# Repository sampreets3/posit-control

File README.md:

# posit-control

Posit is an STM32-based DC motor controller designed to provide an efficient and reliable solution for controlling DC motors in various applications. This README file provides an overview of the Posit motor controller, its features, and instructions on getting started and using it in your projects.

---

## Features

- __STM32F1 Microcontroller:__ Posit is built around the STM32F103 microcontroller, known for its reliability and high-performance capabilities.

__USB Control:__ Posit acts as a USB Virtual COM Port, for sending over commands via usb->serial interfaces.

__UART Communication:__ UART interface for communication with external devices or microcontrollers.

---

## Usage

The Posit STM32 DC Motor Controller is highly customizable to fit a wide range of applications. You can control the motor speed and direction using PWM signals, monitor current feedback, and interface with external sensors for more advanced control.

Here is a basic example of controlling a motor using Posit:

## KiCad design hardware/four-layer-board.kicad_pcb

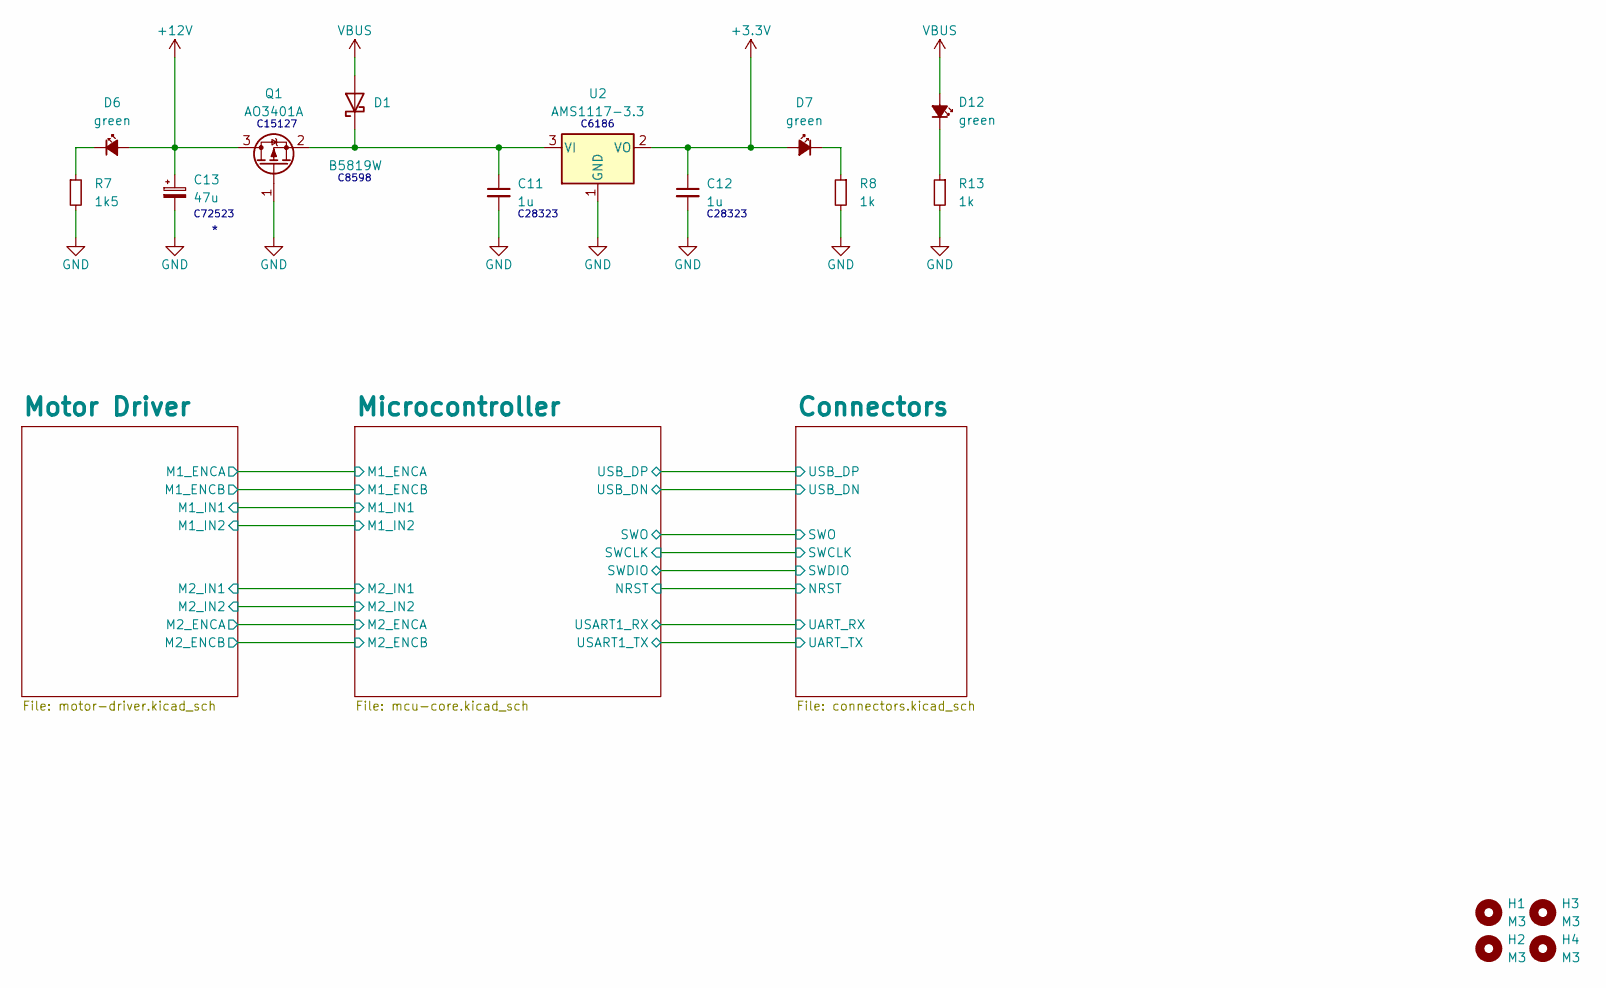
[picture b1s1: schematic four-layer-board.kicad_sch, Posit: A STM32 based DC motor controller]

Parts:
C11, C12: 1u; C_0805_2012Metric
C13: 47u; CP_Elec_6.3x7.7
D1: B5819W; D_SOD-123
D6, D7, D12: green; LED_0603_1608Metric
H1, H2, H3, H4: M3; MountingHole_3.2mm_M3_DIN965_Pad
Q1: AO3401A; SOT-23
R7: 1k5; R_0603_1608Metric
R8, R13: 1k; R_0603_1608Metric
U2: AMS1117-3.3; SOT-223-3_TabPin2

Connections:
+3.3V: C12.1, D7.2 (A), U2.2 (VO); also elsewhere on the board
+12V: C13.1, D6.2 (A), Q1.3 (D); also elsewhere on the board
GND: C11.2, C12.2, C13.2, Q1.1 (G), R7.2, R8.2, R13.2, U2.1 (GND); also elsewhere on the board
unnamed: C11.1, D1.1 (K), Q1.2 (S), U2.3 (VI)
unnamed: D6.1 (K), R7.1
unnamed: D7.1 (K), R8.1
unnamed: D12.1 (K), R13.1
VBUS: D1.2 (A), D12.2 (A); also elsewhere on the board

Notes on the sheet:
C28323
C6186
C15127
C8598
C72523

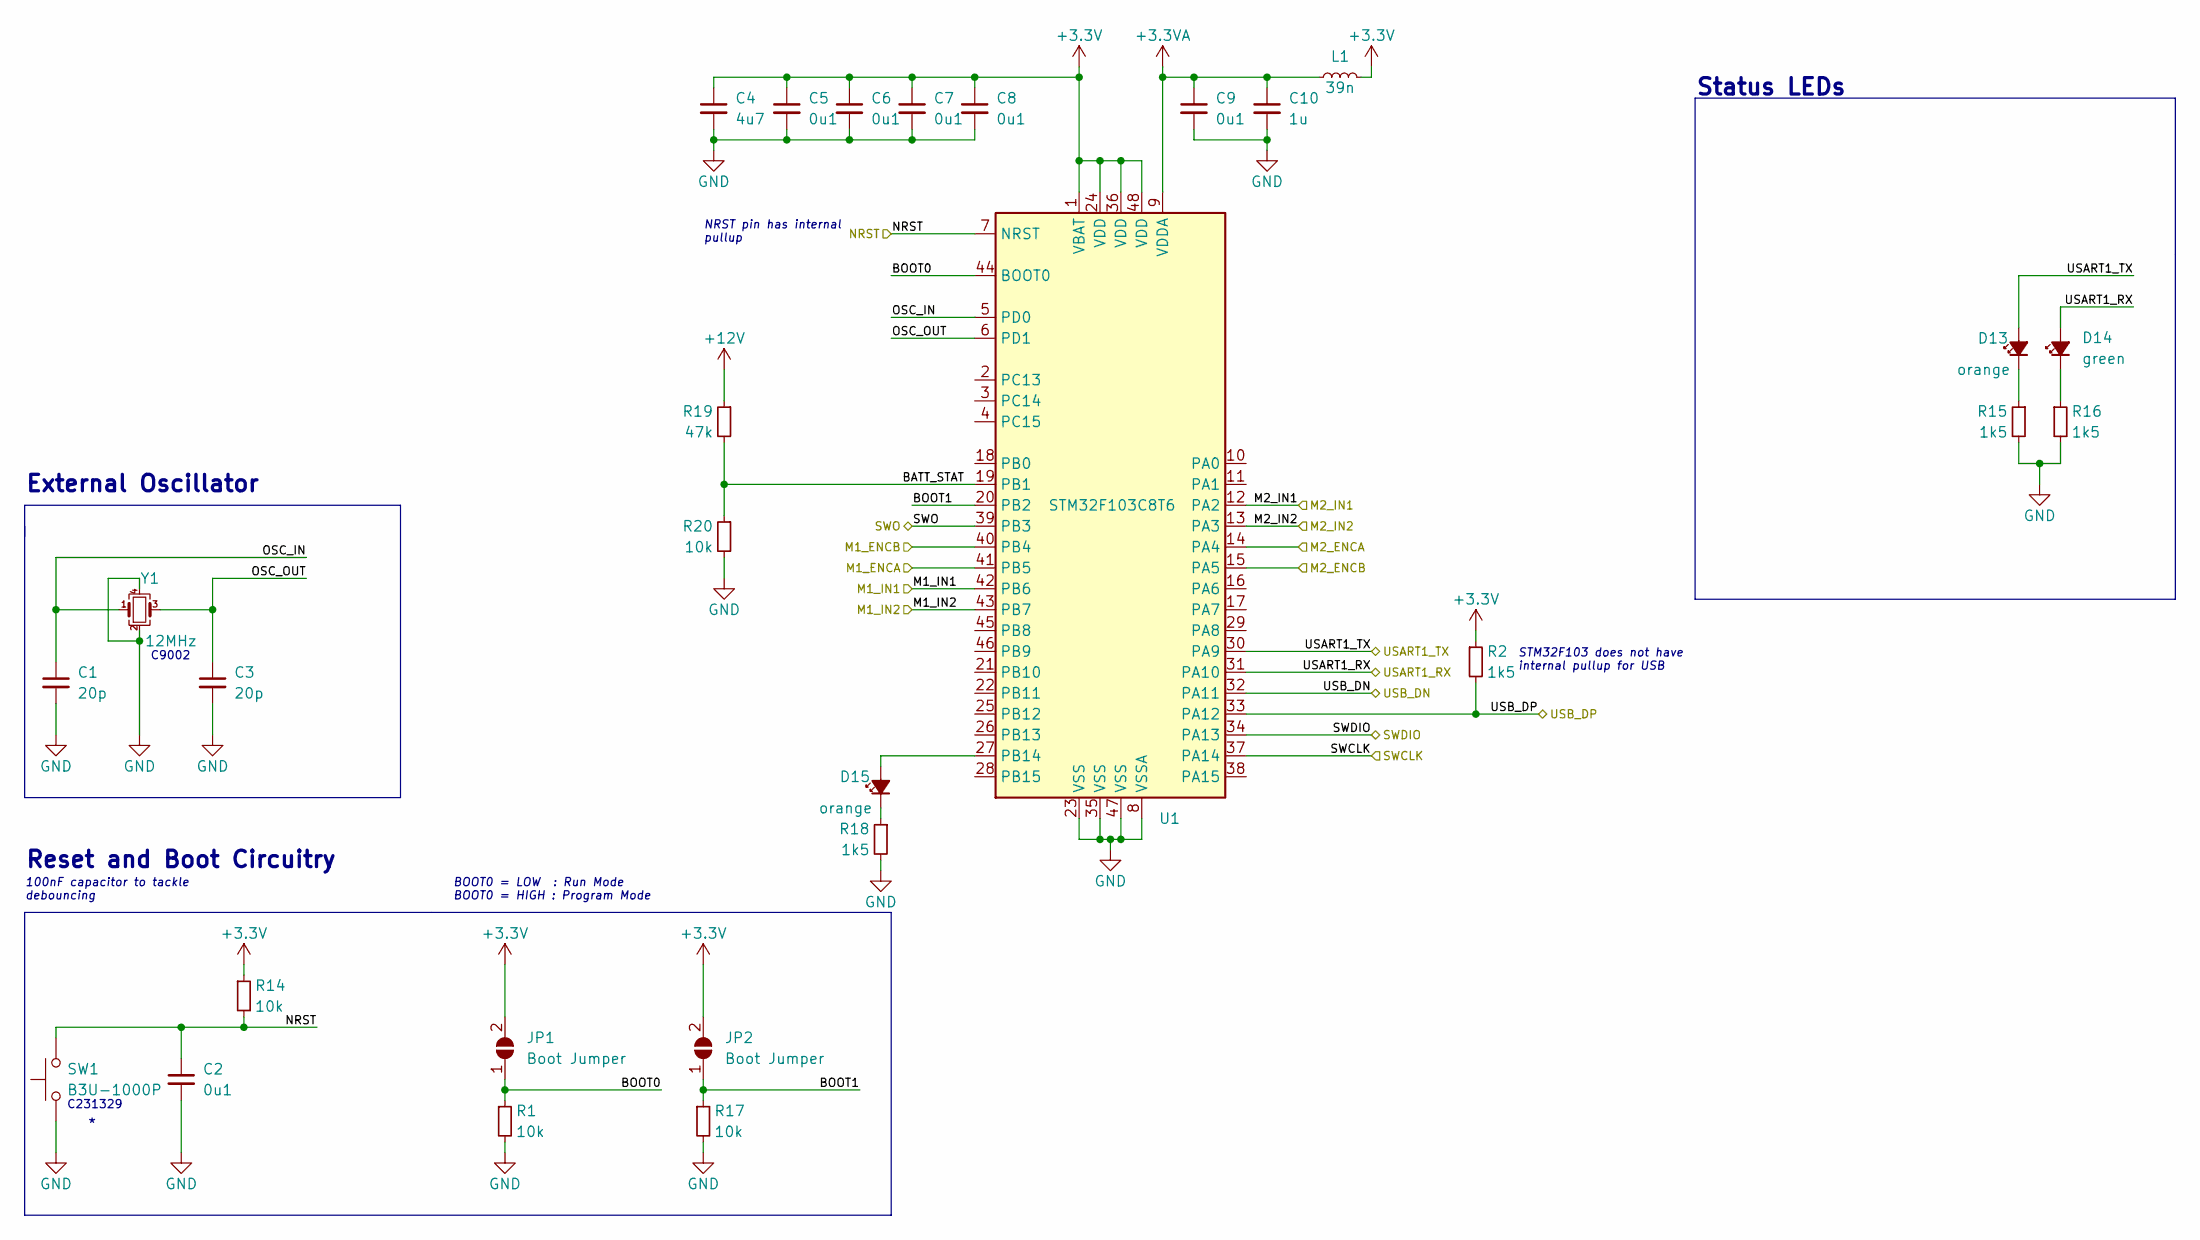
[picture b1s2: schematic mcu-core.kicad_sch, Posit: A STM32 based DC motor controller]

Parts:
C1, C3: 20p; C_0402_1005Metric
C2, C5, C6, C7, C8, C9: 0u1; C_0402_1005Metric
C4: 4u7; C_0603_1608Metric
C10: 1u; C_0402_1005Metric
D13, D15: orange; LED_0603_1608Metric
D14: green; LED_0603_1608Metric
JP1, JP2: Boot Jumper; SolderJumper-2_P1.3mm_Open_Pad1.0x1.5mm
L1: 39n; L_0603_1608Metric
R1, R14, R17: 10k; R_0402_1005Metric
R2, R15, R16, R18: 1k5; R_0402_1005Metric
R19: 47k; R_0603_1608Metric_Pad0.98x0.95mm_HandSolder
R20: 10k; R_0603_1608Metric_Pad0.98x0.95mm_HandSolder
SW1: B3U-1000P; SW_SPST_B3U-1000P
U1: STM32F103C8T6; LQFP-48_7x7mm_P0.5mm
Y1: 12MHz; Crystal_SMD_3225-4Pin_3.2x2.5mm

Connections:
+3.3V: C4.1, C5.1, C6.1, C7.1, C8.1, JP1.2 (B), JP2.2 (B), L1.2, R2.1, R14.1, U1.1 (VBAT), U1.24 (VDD), U1.36 (VDD), U1.48 (VDD); also elsewhere on the board
+3.3VA: C9.1, C10.1, L1.1, U1.9 (VDDA)
+12V: R19.1; also elsewhere on the board
/Microcontroller/BATT_STAT: R19.2, R20.1, U1.19 (PB1)
/Microcontroller/BOOT0: JP1.1 (A), R1.1, U1.44 (BOOT0)
/Microcontroller/BOOT1: JP2.1 (A), R17.1, U1.20 (PB2)
/Microcontroller/M1_ENCA: U1.41 (PB5); also elsewhere on the board
/Microcontroller/M1_ENCB: U1.40 (PB4); also elsewhere on the board
/Microcontroller/M1_IN1: U1.42 (PB6); also elsewhere on the board
/Microcontroller/M1_IN2: U1.43 (PB7); also elsewhere on the board
/Microcontroller/M2_ENCA: U1.14 (PA4); also elsewhere on the board
/Microcontroller/M2_ENCB: U1.15 (PA5); also elsewhere on the board
/Microcontroller/M2_IN1: U1.12 (PA2); also elsewhere on the board
/Microcontroller/M2_IN2: U1.13 (PA3); also elsewhere on the board
/Microcontroller/NRST: C2.1, R14.2, SW1.2, U1.7 (NRST); also elsewhere on the board
/Microcontroller/OSC_IN: C1.1, U1.5 (PD0), Y1.1
/Microcontroller/OSC_OUT: C3.1, U1.6 (PD1), Y1.3
/Microcontroller/SWCLK: U1.37 (PA14); also elsewhere on the board
/Microcontroller/SWDIO: U1.34 (PA13); also elsewhere on the board
/Microcontroller/SWO: U1.39 (PB3); also elsewhere on the board
/Microcontroller/USART1_RX: D14.2 (A), U1.31 (PA10); also elsewhere on the board
/Microcontroller/USART1_TX: D13.2 (A), U1.30 (PA9); also elsewhere on the board
/Microcontroller/USB_DN: U1.32 (PA11); also elsewhere on the board
/Microcontroller/USB_DP: R2.2, U1.33 (PA12); also elsewhere on the board
GND: C1.2, C2.2, C3.2, C4.2, C5.2, C6.2, C7.2, C8.2, C9.2, C10.2, R1.2, R15.2, R16.2, R17.2, R18.2, R20.2, SW1.1, U1.8 (VSSA), U1.23 (VSS), U1.35 (VSS), U1.47 (VSS), Y1.2, Y1.4; also elsewhere on the board
unnamed: D13.1 (K), R15.1
unnamed: D14.1 (K), R16.1
unnamed: D15.2 (A), U1.27 (PB14)
unnamed: D15.1 (K), R18.1

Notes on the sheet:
External Oscillator
STM32F103 does not have internal pullup for USB
100nF capacitor to tackle debouncing
Status LEDs
NRST pin has internal pullup
Reset and Boot Circuitry
C9002
C231329
BOOT0 = LOW : Run Mode BOOT0 = HIGH : Program Mode

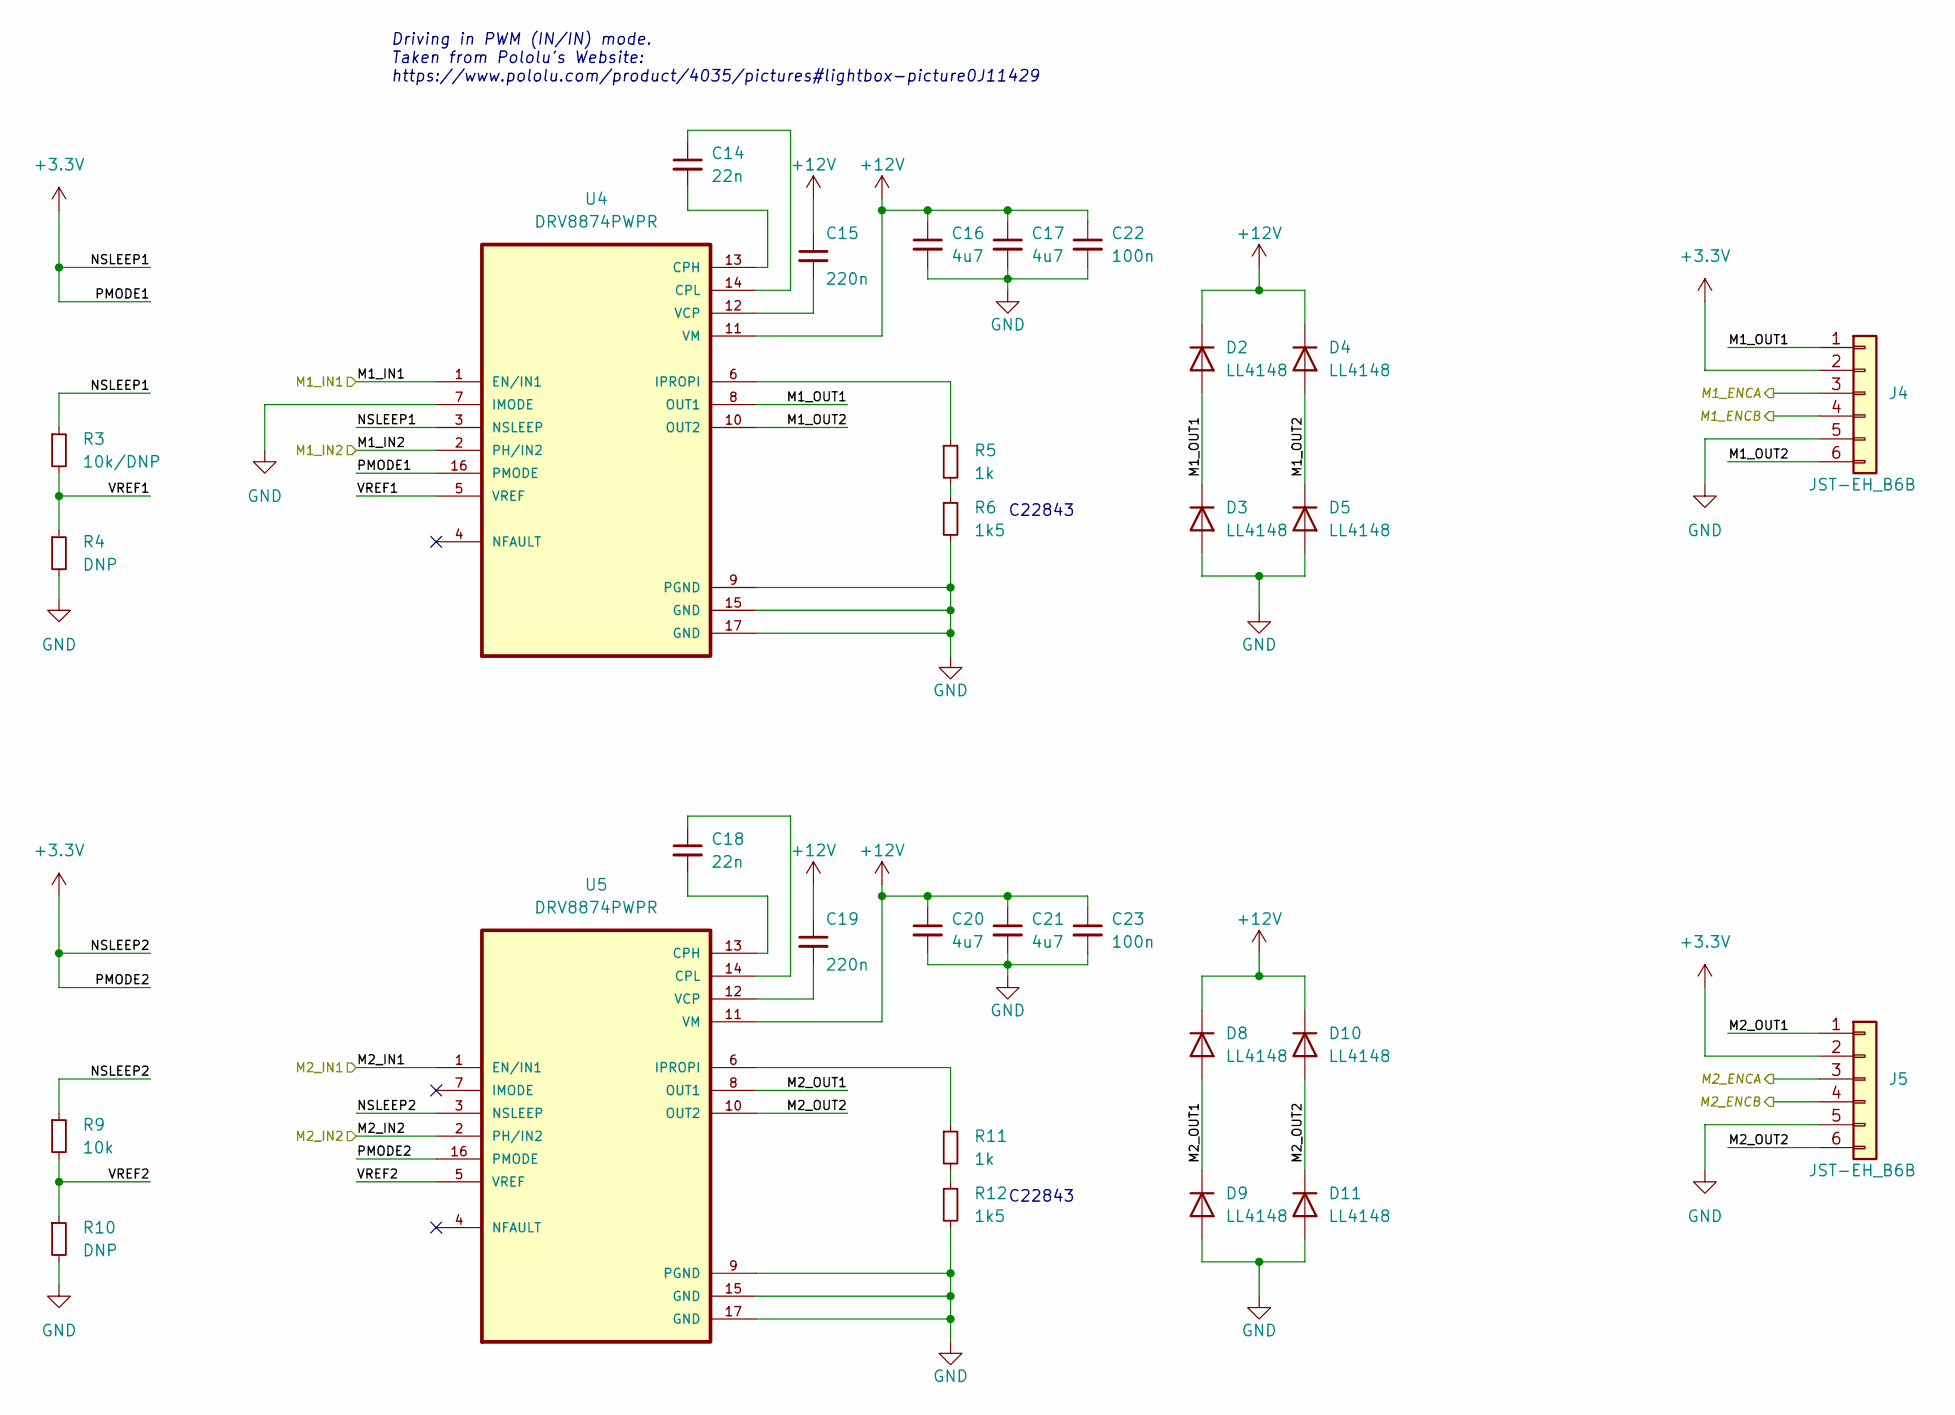
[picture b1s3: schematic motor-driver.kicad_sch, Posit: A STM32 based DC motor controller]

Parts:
C14, C18: 22n; C_0603_1608Metric
C15, C19: 220n; C_0603_1608Metric
C16, C17, C20, C21: 4u7; C_0805_2012Metric
C22, C23: 100n; C_0603_1608Metric
D2, D3, D4, D5, D8, D9, D10, D11: LL4148; D_MiniMELF
J4, J5: JST-EH_B6B; JST_EH_B6B-EH-A_1x06_P2.50mm_Vertical
R3: 10k/DNP; R_0603_1608Metric
R4, R10: DNP; R_0603_1608Metric
R5, R11: 1k; R_0603_1608Metric
R6, R12: 1k5; R_0603_1608Metric
R9: 10k; R_0603_1608Metric
U4, U5: DRV8874PWPR; SOP65P640X120-17N

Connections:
+3.3V: J4.2, J5.2, R3.1, R9.1, U4.3 (NSLEEP), U4.16 (PMODE), U5.3 (NSLEEP), U5.16 (PMODE); also elsewhere on the board
+12V: C15.1, C16.1, C17.1, C19.1, C20.1, C21.1, C22.1, C23.1, D2.1 (K), D4.1 (K), D8.1 (K), D10.1 (K), U4.11 (VM), U5.11 (VM); also elsewhere on the board
/Microcontroller/M1_ENCA: J4.3; also elsewhere on the board
/Microcontroller/M1_ENCB: J4.4; also elsewhere on the board
/Microcontroller/M1_IN1: U4.1 (EN/IN1); also elsewhere on the board
/Microcontroller/M1_IN2: U4.2 (PH/IN2); also elsewhere on the board
/Microcontroller/M2_ENCA: J5.3; also elsewhere on the board
/Microcontroller/M2_ENCB: J5.4; also elsewhere on the board
/Microcontroller/M2_IN1: U5.1 (EN/IN1); also elsewhere on the board
/Microcontroller/M2_IN2: U5.2 (PH/IN2); also elsewhere on the board
/Motor Driver/M1_OUT1: D2.2 (A), D3.1 (K), J4.1, U4.8 (OUT1)
/Motor Driver/M1_OUT2: D4.2 (A), D5.1 (K), J4.6, U4.10 (OUT2)
/Motor Driver/M2_OUT1: D8.2 (A), D9.1 (K), J5.1, U5.8 (OUT1)
/Motor Driver/M2_OUT2: D10.2 (A), D11.1 (K), J5.6, U5.10 (OUT2)
/Motor Driver/VREF1: R3.2, R4.1, U4.5 (VREF)
/Motor Driver/VREF2: R9.2, R10.1, U5.5 (VREF)
GND: C16.2, C17.2, C20.2, C21.2, C22.2, C23.2, D3.2 (A), D5.2 (A), D9.2 (A), D11.2 (A), J4.5, J5.5, R4.2, R6.2, R10.2, R12.2, U4.7 (IMODE), U4.9 (PGND), U4.15 (GND), U4.17 (GND), U5.9 (PGND), U5.15 (GND), U5.17 (GND); also elsewhere on the board
unnamed: R5.2, R6.1
unnamed: R11.2, R12.1
unnamed: C14.2, U4.13 (CPH)
unnamed: C14.1, U4.14 (CPL)
unnamed: R5.1, U4.6 (IPROPI)
unnamed: C15.2, U4.12 (VCP)
unnamed: C18.2, U5.13 (CPH)
unnamed: C18.1, U5.14 (CPL)
unnamed: R11.1, U5.6 (IPROPI)
unnamed: C19.2, U5.12 (VCP)

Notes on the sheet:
C22843
Driving in PWM (IN/IN) mode. Taken from Pololu's Website: https://www.pololu.com/product/4035/pictures#lightbox-picture0J11429

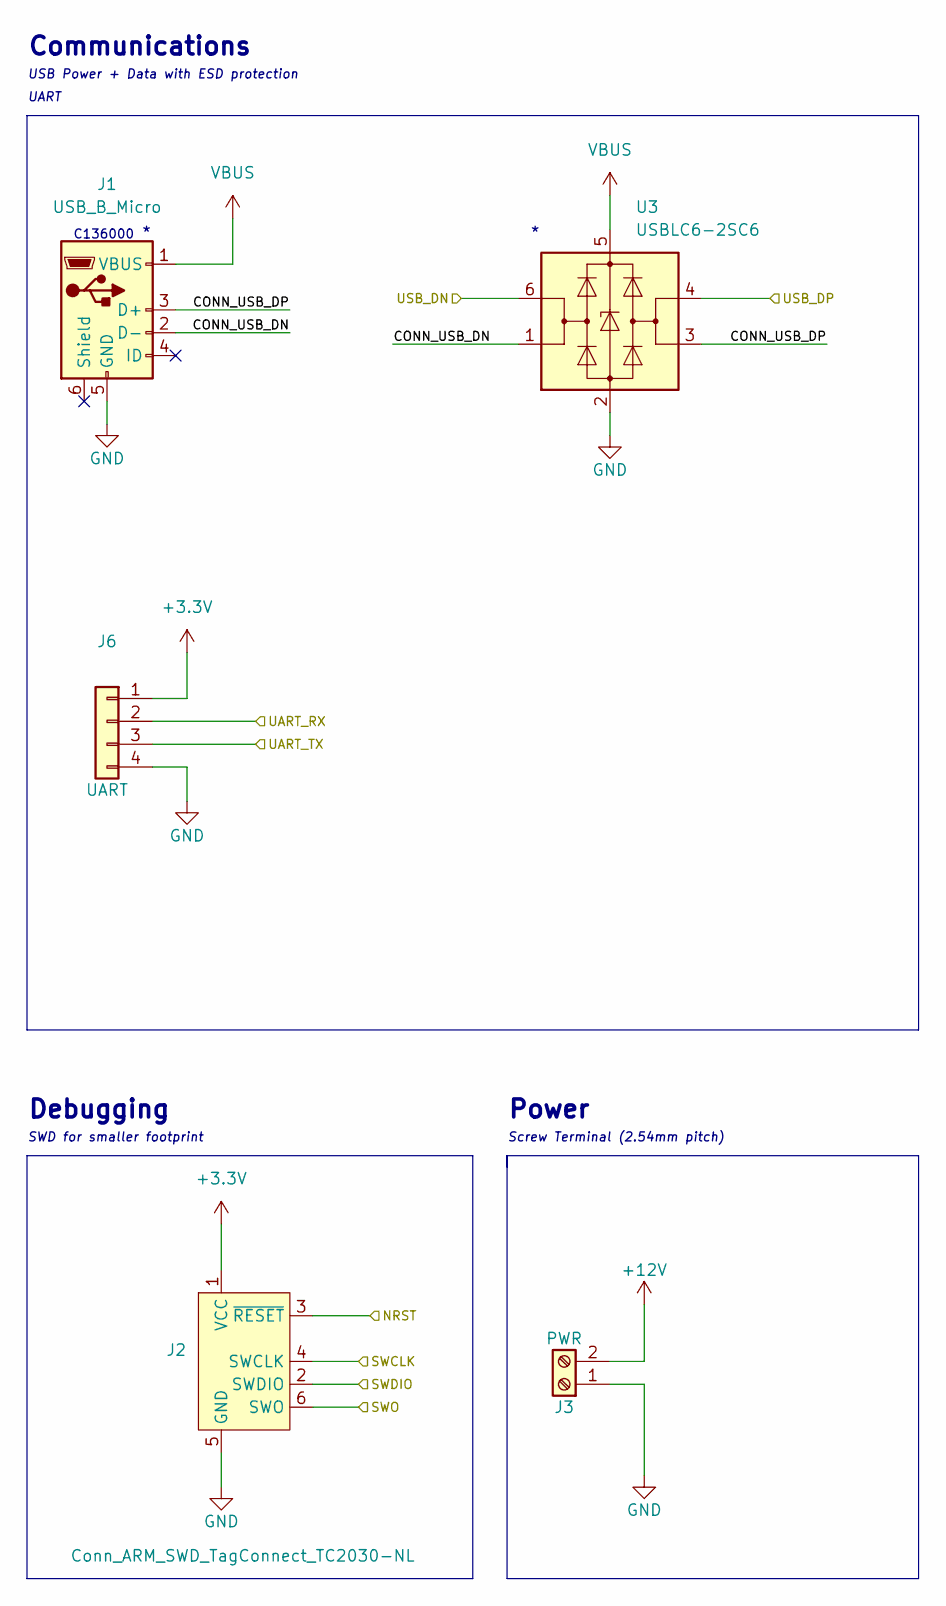
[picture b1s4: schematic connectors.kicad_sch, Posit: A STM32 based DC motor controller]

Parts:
J1: USB_B_Micro; USB_Micro-B_Molex-105017-0001
J2: Conn_ARM_SWD_TagConnect_TC2030-NL; Tag-Connect_TC2030-IDC-NL_2x03_P1.27mm_Vertical
J3: PWR; TerminalBlock_Phoenix_MPT-0,5-2-2.54_1x02_P2.54mm_Horizontal
J6: UART; JST_PH_S4B-PH-K_1x04_P2.00mm_Horizontal
U3: USBLC6-2SC6; SOT-23-6

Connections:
+3.3V: J2.1 (VCC), J6.1; also elsewhere on the board
+12V: J3.2; also elsewhere on the board
/Connectors/CONN_USB_DN: J1.2 (D-), U3.1 (I/O1)
/Connectors/CONN_USB_DP: J1.3 (D+), U3.3 (I/O2)
/Microcontroller/NRST: J2.3 (~RESET); also elsewhere on the board
/Microcontroller/SWCLK: J2.4 (SWCLK); also elsewhere on the board
/Microcontroller/SWDIO: J2.2 (SWDIO); also elsewhere on the board
/Microcontroller/SWO: J2.6 (SWO); also elsewhere on the board
/Microcontroller/USART1_RX: J6.2; also elsewhere on the board
/Microcontroller/USART1_TX: J6.3; also elsewhere on the board
/Microcontroller/USB_DN: U3.6 (I/O1); also elsewhere on the board
/Microcontroller/USB_DP: U3.4 (I/O2); also elsewhere on the board
GND: J1.5 (GND), J2.5 (GND), J3.1, J6.4, U3.2 (GND); also elsewhere on the board
VBUS: J1.1 (VBUS), U3.5 (VBUS); also elsewhere on the board

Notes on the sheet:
Debugging
UART
C136000
Power
SWD for smaller footprint
USB Power + Data with ESD protection
Communications
Screw Terminal (2.54mm pitch)

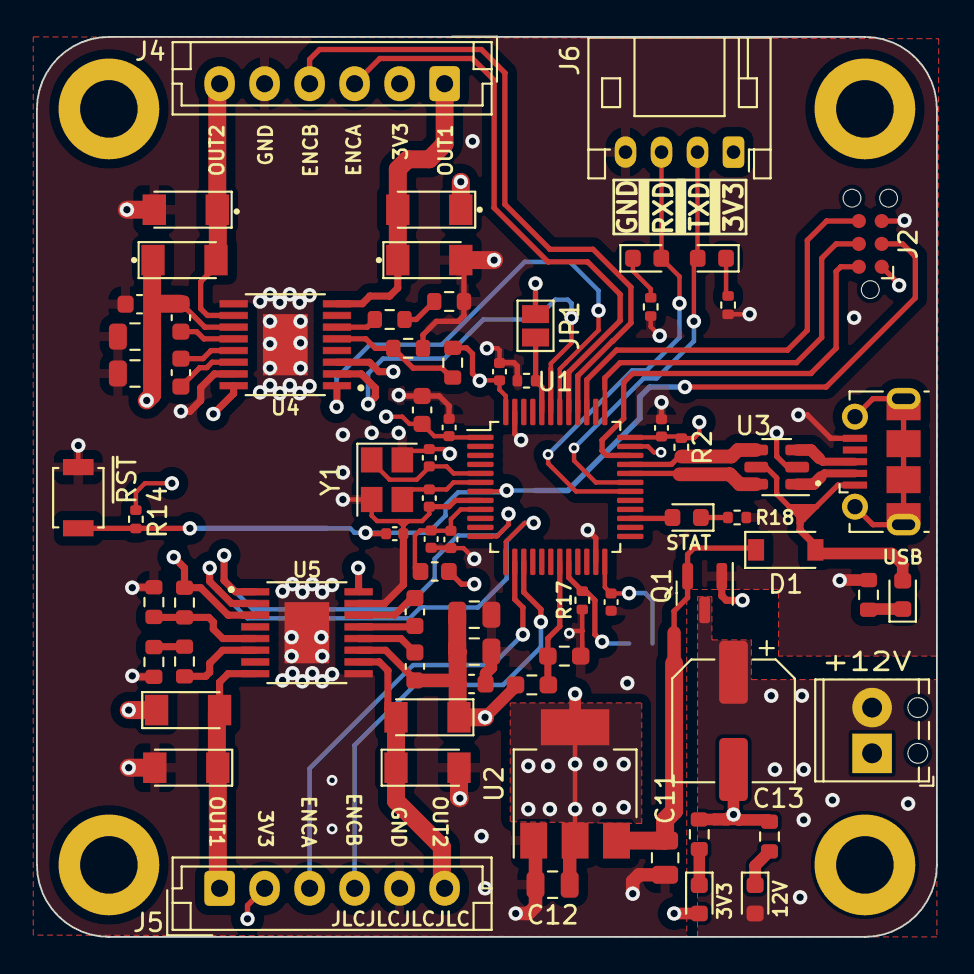
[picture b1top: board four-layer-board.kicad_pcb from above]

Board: 4 copper layers, 50.0 x 50.0 mm, 79 parts (1 on the bottom side), 52 nets.

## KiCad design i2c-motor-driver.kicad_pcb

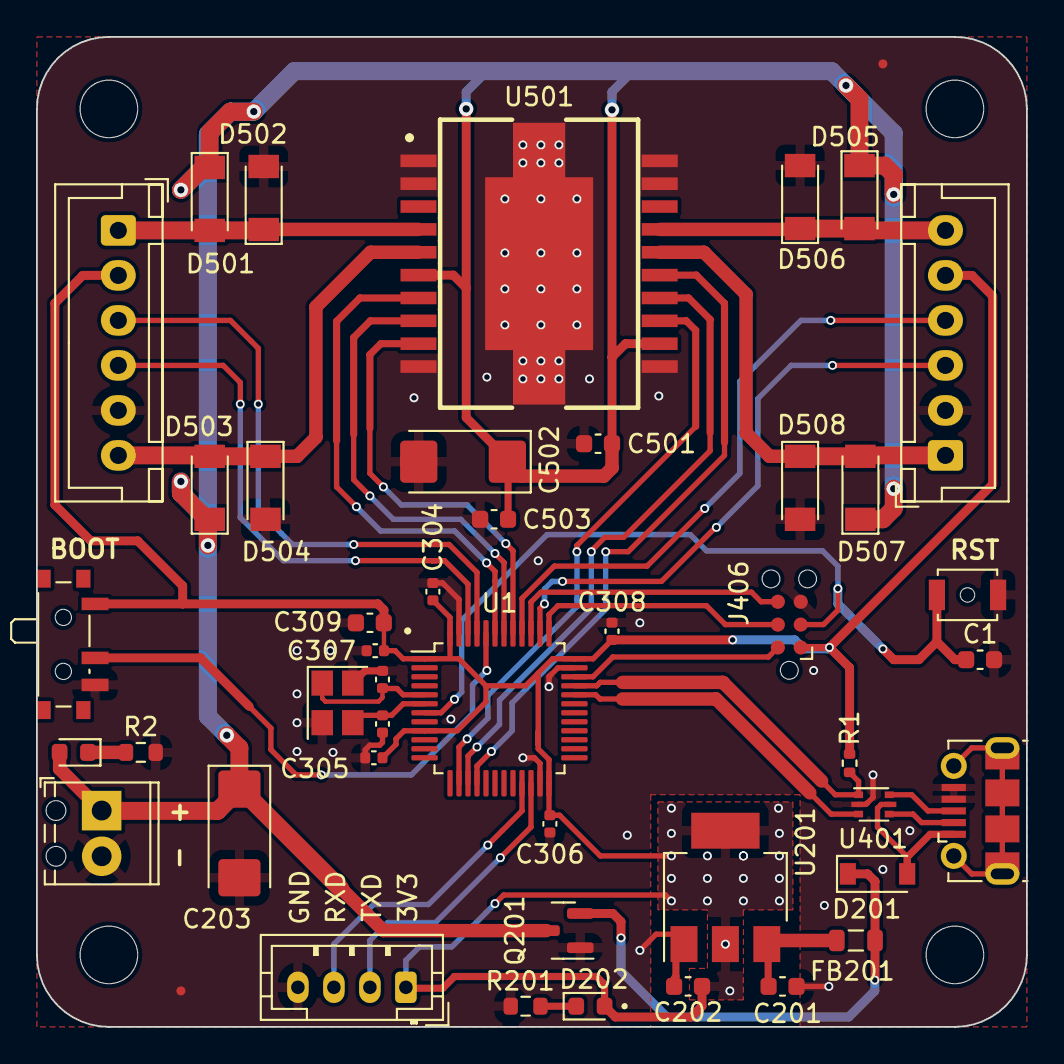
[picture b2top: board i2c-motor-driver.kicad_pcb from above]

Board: 2 copper layers, 55.0 x 55.0 mm, 50 parts (0 on the bottom side), 35 nets.

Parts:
C1: 0u1; C_0603_1608Metric
C201, C202, C501, C503: 10u; C_0603_1608Metric
C203, C502: 22u; CP_EIA-6032-15_Kemet-U
C304, C305, C306, C307, C308: 0u1; C_0402_1005Metric
C309: 4u7; C_0603_1608Metric
C310, C311: 20p; C_0402_1005Metric
D1, D202: green; LED_0603_1608Metric
D201: B5819W; D_SOD-123
D501, D502, D503, D504, D505, D506, D507, D508: LL4148; D_MiniMELF
FB201: 100@100MHz; L_0805_2012Metric
FID401, FID402: Fiducial; Fiducial_0.5mm_Mask1.5mm
H401, H402, H403, H404: M3; MountingHole_3.2mm_M3
J401: PWR_MOTOR; TerminalBlock_Phoenix_MPT-0,5-2-2.54_1x02_P2.54mm_Horizontal
J402: USB_B_Micro; USB_Micro-B_Molex-105017-0001
J403: Motor 1; JST_XH_B6B-XH-A_1x06_P2.50mm_Vertical
J404: I2C Connector; JST_PH_B4B-PH-K_1x04_P2.00mm_Vertical
J405: Motor 2; JST_XH_B6B-XH-A_1x06_P2.50mm_Vertical
J406: Conn_ARM_SWD_TagConnect_TC2030-NL; Tag-Connect_TC2030-IDC-NL_2x03_P1.27mm_Vertical
Q201: AO3401A; SOT-23
R1: 1k5; R_0402_1005Metric
R2: 1k5; R_0603_1608Metric
R201: 510; R_0603_1608Metric
SW1: SW_Push; SW_SPST_B3U-1000P-B
SW2: SW_SPDT; SW_SPDT_PCM12
U1: STM32F103C8Tx; LQFP-48_7x7mm_P0.5mm
U201: AMS1117-3.3; SOT-223-3_TabPin2
U401: USBLC6-2P6; SOT-666
U501: L298P; SOIC127P1420X360-20N
Y301: 12MHz; Crystal_SMD_3225-4Pin_3.2x2.5mm

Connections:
+3V3: C202.1, C304.1, C305.1, C306.1, C307.1, C308.1, C309.1, D202.2 (A), J403.2, J404.1, J405.5, J406.1 (VCC), R1.1, SW2.1 (A), U1.1 (VBAT), U1.9 (VDDA), U1.24 (VDD), U1.36 (VDD), U1.48 (VDD), U201.2 (VO)
+12V: C203.1, C501.1, C502.1, C503.1, D1.2 (A), D501.1 (K), D503.1 (K), D505.1 (K), D507.1 (K), J401.1, Q201.3 (D), U501.6 (VS), U501.12 (VSS)
/Connectors/CONN_USB_DN: U1.32 (PA11), U401.3 (I/O2)
/Connectors/CONN_USB_DP: R1.2, U1.33 (PA12), U401.1 (I/O1)
/Connectors/M1_OUT1: D501.2 (A), D502.1 (K), J403.1, U501.4 (OUT1)
/Connectors/M1_OUT2: D503.2 (A), D504.1 (K), J403.6, U501.5 (OUT2)
/Connectors/M2_OUT1: D505.2 (A), D506.1 (K), J405.6, U501.17 (OUT4)
/Connectors/M2_OUT2: D507.2 (A), D508.1 (K), J405.1, U501.16 (OUT3)
/Connectors/UART_RX: J404.3, U1.21 (PB10)
/Connectors/UART_TX: J404.2, U1.22 (PB11)
/Connectors/USB_CONN_DN: J402.2 (D-), U401.4 (I/O2)
/Connectors/USB_CONN_DP: J402.3 (D+), U401.6 (I/O1)
/Microcontroller/BOOT0: SW2.2 (B), U1.44 (BOOT0)
/Microcontroller/M1_EN1: U1.42 (PB6), U501.8 (ENA)
/Microcontroller/M1_ENCA: J403.3, U1.45 (PB8)
/Microcontroller/M1_ENCB: J403.4, U1.46 (PB9)
/Microcontroller/M1_IN1: U1.43 (PB7), U501.7 (IN1)
/Microcontroller/M1_IN2: U1.41 (PB5), U501.9 (IN2)
/Microcontroller/M2_EN1: U1.15 (PA5), U501.14 (ENB)
/Microcontroller/M2_ENCA: J405.4, U1.40 (PB4)
/Microcontroller/M2_ENCB: J405.3, U1.38 (PA15)
/Microcontroller/M2_IN1: U1.16 (PA6), U501.15 (IN4)
/Microcontroller/M2_IN2: U1.14 (PA4), U501.13 (IN3)
/Microcontroller/NRST: C1.1, J406.3 (~RESET), SW1.1, U1.7 (NRST)
/Microcontroller/OSC_IN: C310.1, U1.5 (PD0), Y301.1
/Microcontroller/OSC_OUT: C311.1, U1.6 (PD1), Y301.3
/Microcontroller/SWCLK: J406.4 (SWCLK), U1.37 (PA14)
/Microcontroller/SWDIO: J406.2 (SWDIO), U1.34 (PA13)
/Microcontroller/SWO: J406.6 (SWO), U1.39 (PB3)
GND: C1.2, C201.2, C202.2, C203.2, C304.2, C305.2, C306.2, C307.2, C308.2, C309.2, C310.2, C311.2, C501.2, C502.2, C503.2, D502.2 (A), D504.2 (A), D506.2 (A), D508.2 (A), J401.2, J402.4 (ID), J402.5 (GND), J403.5, J404.4, J405.2, J406.5 (GND), Q201.1 (G), R2.2, R201.2, SW1.2, SW2.3 (C), U1.23 (VSS), U1.35 (VSS), U1.47 (VSS), U201.1 (GND), U401.2 (GND), U501.1 (GND), U501.2 (SENA), U501.10 (GND), U501.11 (GND), U501.19 (SENB), U501.20 (GND), U501.21 (PAD), U501.22 (PAD), U501.23 (PAD), Y301.2, Y301.4
unnamed: C201.1, FB201.2, U201.3 (VI)
unnamed: D1.1 (K), R2.1
unnamed: D202.1 (K), R201.1
unnamed: D201.1 (K), FB201.1, Q201.2 (S)
VBUS: D201.2 (A), J402.1 (VBUS), U401.5 (VBUS)

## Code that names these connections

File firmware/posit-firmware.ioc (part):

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Mcu.Name=STM32F103C(8-B)Tx
Mcu.Package=LQFP48
Mcu.UserName=STM32F103C8Tx
PA10.Mode=Asynchronous
PA10.Signal=USART1_RX
PA11.Mode=Device
PA11.Signal=USB_DM
PA12.Mode=Device
PA12.Signal=USB_DP
PA13.Mode=Trace_Asynchronous_SW
PA13.Signal=SYS_JTMS-SWDIO
PA14.Mode=Trace_Asynchronous_SW
PA14.Signal=SYS_JTCK-SWCLK
PA2.GPIOParameters=GPIO_Label
PA2.GPIO_Label=M2_IN1
PA2.Signal=GPIO_Output
PA3.GPIOParameters=GPIO_Label
PA3.GPIO_Label=M2_IN2
PA3.Signal=GPIO_Output
PA4.GPIOParameters=GPIO_Label
PA4.GPIO_Label=M2_ENCA
PA4.Signal=GPIO_Input
PA5.GPIOParameters=GPIO_Label
PA5.GPIO_Label=M2_ENCB
PA5.Signal=GPIO_Input
PA9.Mode=Asynchronous
PA9.Signal=USART1_TX
PB1.GPIOParameters=GPIO_Label
PB1.GPIO_Label=BATT_STAT
PB1.Signal=ADCx_IN9
PB14.GPIOParameters=GPIO_Label
PB14.GPIO_Label=STAT_LED
PB14.Signal=GPIO_Output
PB3.Mode=Trace_Asynchronous_SW
PB3.Signal=SYS_JTDO-TRACESWO
PB4.GPIOParameters=GPIO_Label
PB4.GPIO_Label=M1_ENCB
PB4.Signal=GPIO_Input
PB5.GPIOParameters=GPIO_Label
PB5.GPIO_Label=M1_ENCA
PB5.Signal=GPIO_Input
PB6.GPIOParameters=GPIO_Label
PB6.GPIO_Label=M1_IN1
PB6.Signal=GPIO_Output
PB7.GPIOParameters=GPIO_Label
PB7.GPIO_Label=M1_IN2
PB7.Signal=GPIO_Output
PD0-OSC_IN.Mode=HSE-External-Oscillator
PD0-OSC_IN.Signal=RCC_OSC_IN
PD1-OSC_OUT.Mode=HSE-External-Oscillator
PD1-OSC_OUT.Signal=RCC_OSC_OUT
RCC.HSE_VALUE=12000000
RCC.SYSCLKFreq_VALUE=12000000
RCC.SYSCLKSource=RCC_SYSCLKSOURCE_HSE
board=custom

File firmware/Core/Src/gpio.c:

/* USER CODE BEGIN Header */
/**
  ******************************************************************************
  * @file    gpio.c
  * @brief   This file provides code for the configuration
  *          of all used GPIO pins.
  ******************************************************************************
  * @attention
  *
  * Copyright (c) 2023 STMicroelectronics.
  * All rights reserved.
  *
  * This software is licensed under terms that can be found in the LICENSE file
  * in the root directory of this software component.
  * If no LICENSE file comes with this software, it is provided AS-IS.
  *
  ******************************************************************************
  */
/* USER CODE END Header */

/* Includes ------------------------------------------------------------------*/
#include "gpio.h"

/* USER CODE BEGIN 0 */

/* USER CODE END 0 */

/*----------------------------------------------------------------------------*/
/* Configure GPIO                                                             */
/*----------------------------------------------------------------------------*/
/* USER CODE BEGIN 1 */

/* USER CODE END 1 */

/** Configure pins as
        * Analog
        * Input
        * Output
        * EVENT_OUT
        * EXTI
        * Free pins are configured automatically as Analog (this feature is enabled through
        * the Code Generation settings)
*/
void MX_GPIO_Init(void)
{

  GPIO_InitTypeDef GPIO_InitStruct = {0};

  /* GPIO Ports Clock Enable */
  __HAL_RCC_GPIOC_CLK_ENABLE();
  __HAL_RCC_GPIOD_CLK_ENABLE();
  __HAL_RCC_GPIOA_CLK_ENABLE();
  __HAL_RCC_GPIOB_CLK_ENABLE();

  /*Configure GPIO pin Output Level */
  HAL_GPIO_WritePin(GPIOA, M2_IN1_Pin|M2_IN2_Pin, GPIO_PIN_RESET);

  /*Configure GPIO pin Output Level */
  HAL_GPIO_WritePin(GPIOB, STAT_LED_Pin|M1_IN1_Pin|M1_IN2_Pin, GPIO_PIN_RESET);

  /*Configure GPIO pins : PC13 PC14 PC15 */
  GPIO_InitStruct.Pin = GPIO_PIN_13|GPIO_PIN_14|GPIO_PIN_15;
  GPIO_InitStruct.Mode = GPIO_MODE_ANALOG;
  HAL_GPIO_Init(GPIOC, &GPIO_InitStruct);

  /*Configure GPIO pins : PA0 PA1 PA6 PA7
                           PA8 PA15 */
  GPIO_InitStruct.Pin = GPIO_PIN_0|GPIO_PIN_1|GPIO_PIN_6|GPIO_PIN_7
                          |GPIO_PIN_8|GPIO_PIN_15;
  GPIO_InitStruct.Mode = GPIO_MODE_ANALOG;
  HAL_GPIO_Init(GPIOA, &GPIO_InitStruct);

  /*Configure GPIO pins : PAPin PAPin */
  GPIO_InitStruct.Pin = M2_IN1_Pin|M2_IN2_Pin;
  GPIO_InitStruct.Mode = GPIO_MODE_OUTPUT_PP;
  GPIO_InitStruct.Pull = GPIO_NOPULL;
  GPIO_InitStruct.Speed = GPIO_SPEED_FREQ_LOW;
  HAL_GPIO_Init(GPIOA, &GPIO_InitStruct);

  /*Configure GPIO pins : PAPin PAPin */
  GPIO_InitStruct.Pin = M2_ENCA_Pin|M2_ENCB_Pin;
  GPIO_InitStruct.Mode = GPIO_MODE_INPUT;
  GPIO_InitStruct.Pull = GPIO_NOPULL;
  HAL_GPIO_Init(GPIOA, &GPIO_InitStruct);

  /*Configure GPIO pins : PB0 PB2 PB10 PB11
                           PB12 PB13 PB15 PB8
                           PB9 */
  GPIO_InitStruct.Pin = GPIO_PIN_0|GPIO_PIN_2|GPIO_PIN_10|GPIO_PIN_11
                          |GPIO_PIN_12|GPIO_PIN_13|GPIO_PIN_15|GPIO_PIN_8
                          |GPIO_PIN_9;
  GPIO_InitStruct.Mode = GPIO_MODE_ANALOG;
  HAL_GPIO_Init(GPIOB, &GPIO_InitStruct);

  /*Configure GPIO pins : PBPin PBPin PBPin */
  GPIO_InitStruct.Pin = STAT_LED_Pin|M1_IN1_Pin|M1_IN2_Pin;
  GPIO_InitStruct.Mode = GPIO_MODE_OUTPUT_PP;
  GPIO_InitStruct.Pull = GPIO_NOPULL;
  GPIO_InitStruct.Speed = GPIO_SPEED_FREQ_LOW;
  HAL_GPIO_Init(GPIOB, &GPIO_InitStruct);

  /*Configure GPIO pins : PBPin PBPin */
  GPIO_InitStruct.Pin = M1_ENCB_Pin|M1_ENCA_Pin;
  GPIO_InitStruct.Mode = GPIO_MODE_INPUT;
  GPIO_InitStruct.Pull = GPIO_NOPULL;
  HAL_GPIO_Init(GPIOB, &GPIO_InitStruct);

}

/* USER CODE BEGIN 2 */

/* USER CODE END 2 */

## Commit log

2023-06-12 Cleanup commit
2023-06-25 Switched to a four layer design
2023-06-25 Modified gitignore
2023-06-25 Added connections for motor 2
2023-06-25 Moved hardware to separate directory
2023-06-25 Added pin assignments in firmware
2023-06-27 Added LEDs and UART
2023-06-28 Added BOOT1 jumper
2023-06-29 Added status LED and silkscreen
2023-07-07 Minor changes, added 100n cap
2023-08-09 Updated hardware design, added TagConnect Probe and Battery Voltage Measurement
2023-09-02 Updated design, ready to generate production files
2023-09-11 Cleaned up debug firmware
2023-09-11 removed Debug firmware
2023-09-11 Added Blinky program
2023-09-11 Fixed missing timer for toggle
2023-09-12 Added USB_DEVICE MiddleWare
2023-11-18 Added middleware implementation of function TransmitDataFrame
2023-12-13 Removed STM32 Project
2023-12-13 Added initial project structure and IOC file
2024-04-04 Added middleware and lower level driver for motor controller
2024-04-04 Removed unncecessary selector and added test scheduler
2024-04-04 Document header added along with missed file for scheduler
2024-04-04 Replaced not working project with a working
2024-04-04 Changes in c project file to include build of scheduler folder
2024-04-04 Edited gitignore to remove debug and setting
2024-04-04 Minor fixes and api added in header file
2024-04-05 Addded back motor selector logic, open loop conditions incorporated.
2024-04-05 Renamed drv_low folder and refactored driver file names
